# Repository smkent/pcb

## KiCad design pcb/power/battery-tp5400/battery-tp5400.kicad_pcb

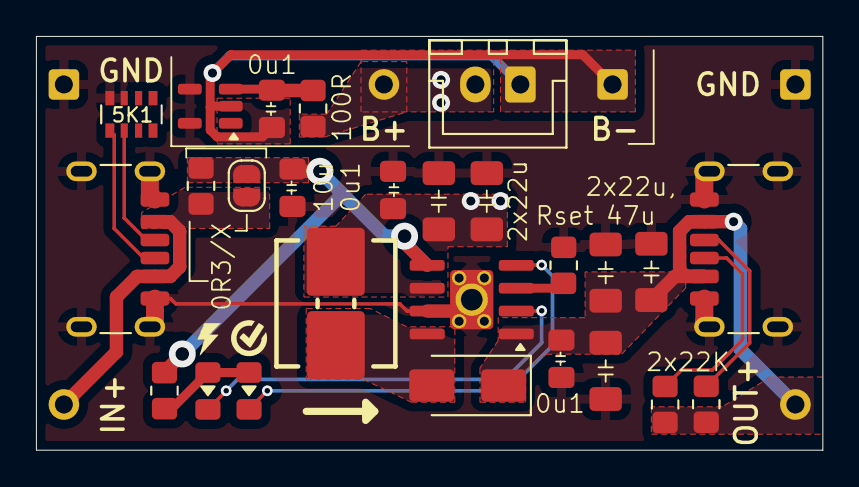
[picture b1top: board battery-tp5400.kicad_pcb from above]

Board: 2 copper layers, 43.7 x 23.0 mm, 32 parts (0 on the bottom side), 16 nets.

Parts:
BT1: Battery_Cell; JST_XH_B2B-XH-A_1x02_P2.50mm_Vertical_simple_pad2gnd
C0: 0.1uF; C_0805_2012Metric_Pad1.18x1.45mm_HandSolder
C1: 10u; C_0805_2012Metric_Pad1.18x1.45mm_HandSolder
C2, C5: 0u1; C_0805_2012Metric_Pad1.18x1.45mm_HandSolder
C3, C4, C6, C7: 22u; C_1206_3216Metric_Pad1.33x1.80mm_HandSolder
C8: 47u; C_1206_3216Metric_Pad1.33x1.80mm_HandSolder
D3: SS34; D_SMA
J0, J7: USB_C_Receptacle_PowerOnly_6P; USB_C_Receptacle_GCT_USB4125-xx-x_6P_TopMnt_Horizontal_hand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
J1, J3, J5: Conn_01x01; PinHeader_1x01_P2.54mm_simple
J2, J4, J6: Conn_01x01; PinHeader_1x01_P2.54mm_simple_square
JP1: SolderJumper_2_Open; SolderJumper-2_P1.3mm_Open_RoundedPad1.0x1.5mm
L2: 10u; Inductor_Multi_7.0x6.6_plus
LED1, LED2: LED; LED_0805_2012Metric_Pad1.15x1.40mm_HandSolder_simple
R0: 0R3; R_0805_2012Metric_Pad1.20x1.40mm_HandSolder
R1: 1K; R_0805_2012Metric_Pad1.20x1.40mm_HandSolder
R2: 100R; R_0805_2012Metric_Pad1.20x1.40mm_HandSolder
R3: 1K1; R_0805_2012Metric_Pad1.20x1.40mm_HandSolder
R4, R5: 22K; R_0805_2012Metric_Pad1.20x1.40mm_HandSolder
RN1: 5K1; R_Array_Convex_4x0603
U1: TP5400_C2891434; SOIC-8-1EP_3.9x4.9mm_P1.27mm_EP2.41x3.3mm_ThermalVias_Custo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
U2: XB5350D0; SOT-23-5_simple

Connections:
B+: BT1.1 (+), C2.2, C3.2, C4.2, J3.1, L2.2, R2.1, U1.6 (BAT)
B-: BT1.2 (-), C0.1, J4.1, U2.2 (GND)
BATVDD: C0.2, R2.2, U2.3 (VDD)
GND: C1.1, C2.1, C3.1, C4.1, C5.1, C6.1, C7.1, C8.1, J0.A12 (GND), J0.B12 (GND), J0.S1 (SHIELD), J2.1, J6.1, J7.A12 (GND), J7.B12 (GND), J7.S1 (SHIELD), R3.1, RN1.7 (R2.2), RN1.8 (R1.2), U1.7 (GND), U1.9 (EP), U2.4 (VM), U2.5 (VM)
LED1: LED1.1 (K), U1.2 (~CHRG)
LED2: LED2.1 (K), U1.4 (~STDBY)
LX: D3.2 (A), L2.1, U1.8 (LX)
unnamed: J0.A5 (CC1), RN1.2 (R2.1)
unnamed: J0.B5 (CC2), RN1.1 (R1.1)
unnamed: J7.A5 (CC1), R4.2
unnamed: J7.B5 (CC2), R5.2
unnamed: LED1.2 (A), LED2.2 (A), R1.2
unnamed: R3.2, U1.3 (PROG)
VCC: J0.A9 (VBUS), J0.B9 (VBUS), J1.1, JP1.2 (B), R0.2
VIN: C1.2, JP1.1 (A), R0.1, R1.1, U1.5 (VCC)
VOUT: C5.2, C6.2, C7.2, C8.2, D3.1 (K), J5.1, J7.A9 (VBUS), J7.B9 (VBUS), R4.1, R5.1, U1.1 (VOUT)

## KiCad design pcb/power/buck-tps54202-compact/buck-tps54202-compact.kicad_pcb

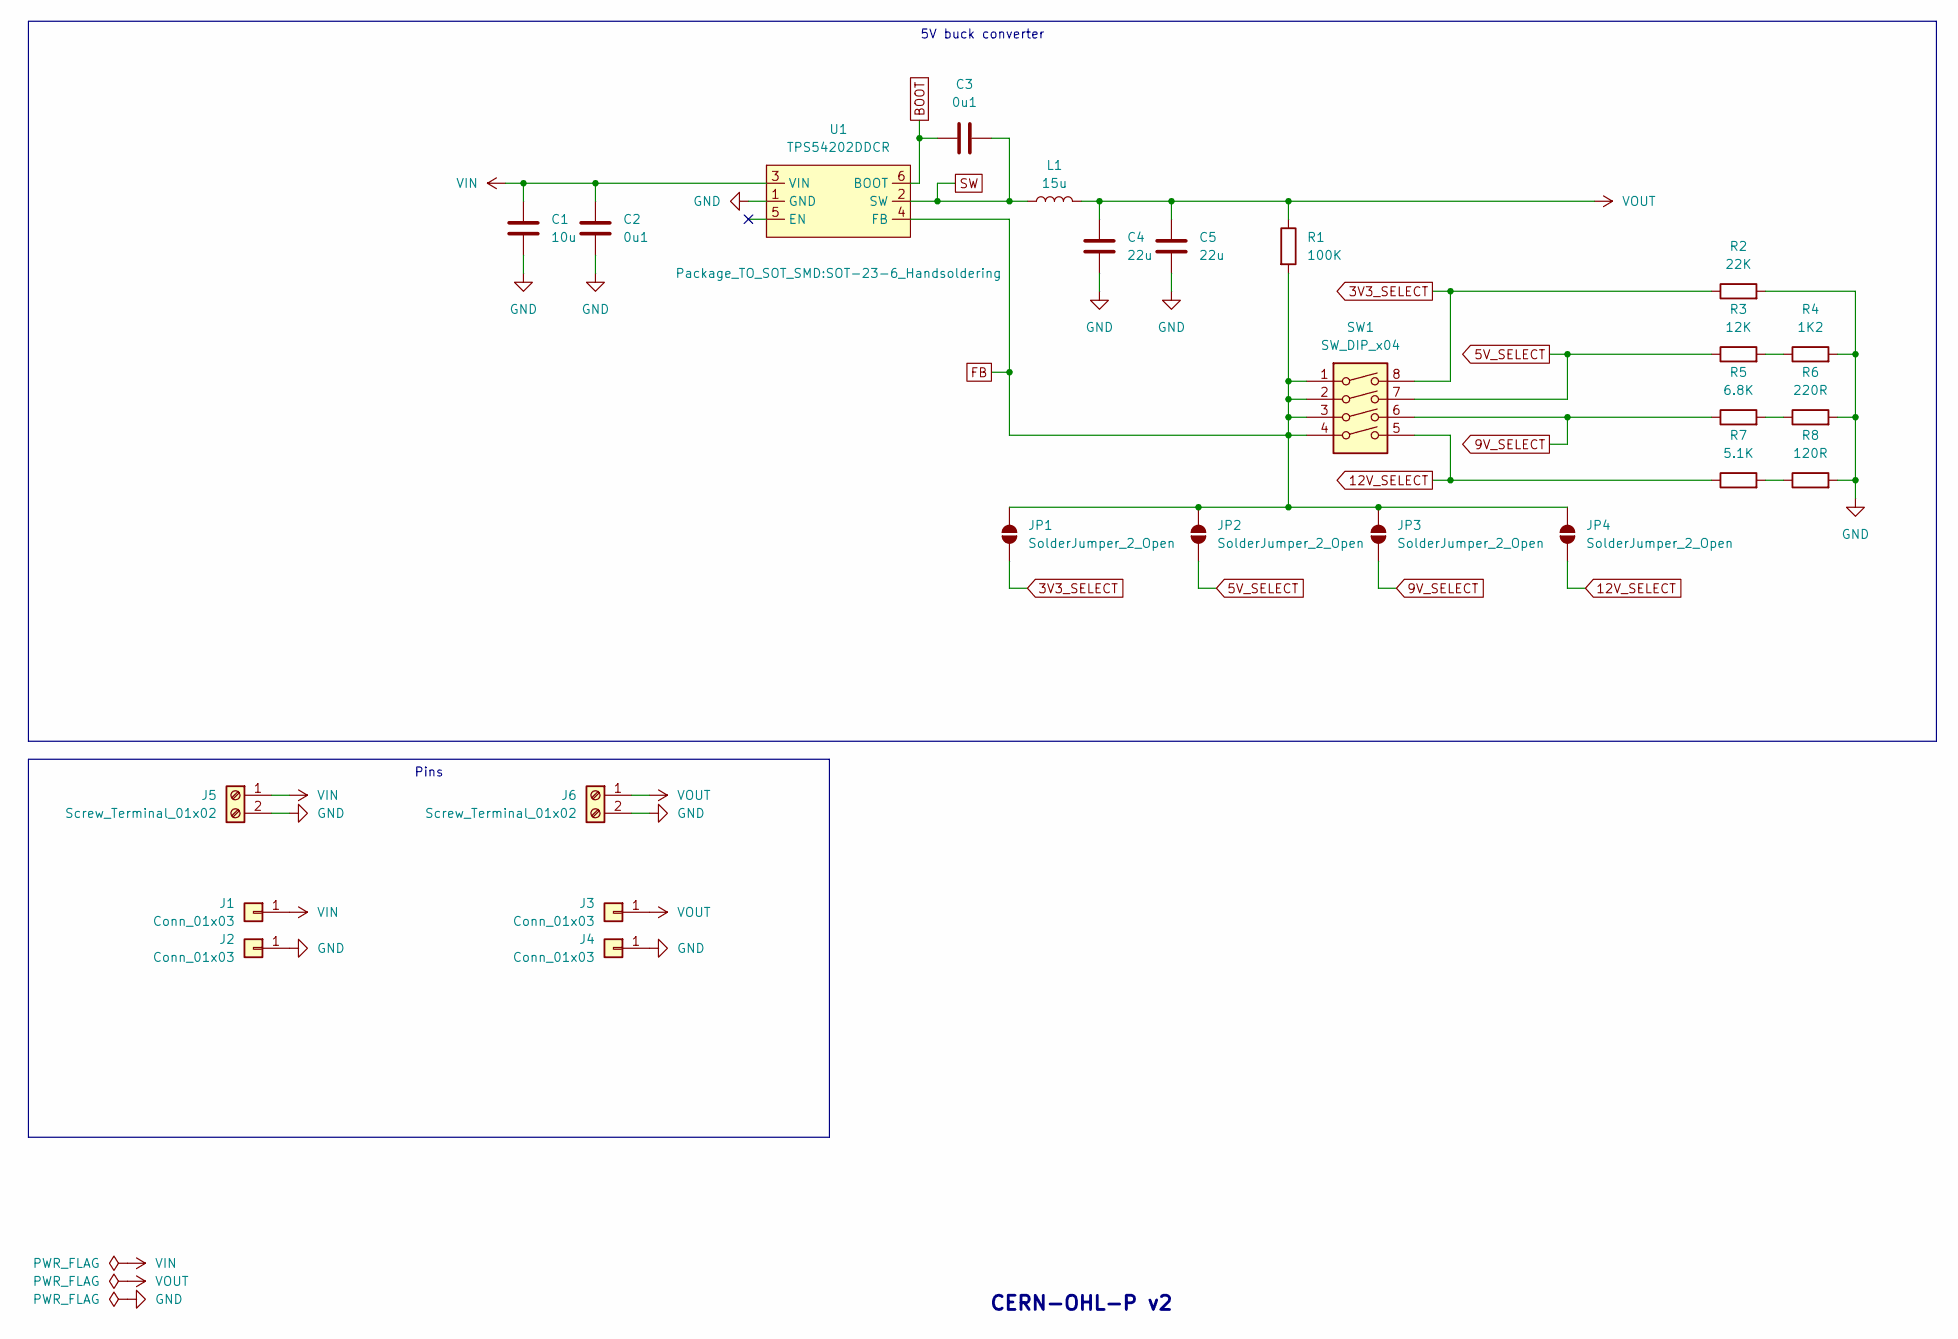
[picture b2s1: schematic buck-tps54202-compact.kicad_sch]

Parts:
C1: 10u; C_0805_2012Metric_Pad1.18x1.45mm_HandSolder; LCSC Part C440198
C2, C3: 0u1; C_0402_1005Metric; LCSC Part C307331
C4, C5: 22u; C_0805_2012Metric_Pad1.18x1.45mm_HandSolder; LCSC Part C45783
J1, J3: Conn_01x03; PinHeader_1x01_P2.54mm_simple
J2, J4: Conn_01x03; PinHeader_1x01_P2.54mm_simple_square
J5, J6: Screw_Terminal_01x02; TerminalBlock_or_JST_2.54_1x02
JP1, JP2, JP3, JP4: SolderJumper_2_Open; SolderJumper-2_P1.3mm_Open_RoundedPad1.0x1.5mm_simple
L1: 15u; Inductor_Multi_5.2x5.7_2x2.5
R1: 100K; R_0402_1005Metric; LCSC Part C25741
R2: 22K; R_0402_1005Metric; LCSC Part C25768
R3: 12K; R_0402_1005Metric; LCSC Part C25752
R4: 1K2; R_0402_1005Metric; LCSC Part C25862
R5: 6.8K; R_0402_1005Metric; LCSC Part C25917
R6: 220R; R_0402_1005Metric; LCSC Part C25091
R7: 5.1K; R_0402_1005Metric; LCSC Part C25905
R8: 120R; R_0402_1005Metric; LCSC Part C25079
SW1: SW_DIP_x04; SW_DIP_SPSTx04_Slide_P1.27mm_simple
U1: TPS54202DDCR; SOT-23-6_Handsoldering; LCSC Part C191884

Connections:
3V3_SELECT: JP1.1 (A), R2.1, SW1.8
5V_SELECT: JP2.1 (A), R3.1, SW1.7
9V_SELECT: JP3.1 (A), R5.1, SW1.6
12V_SELECT: JP4.1 (A), R7.1, SW1.5
BOOT: C3.1, U1.6 (BOOT)
FB: JP1.2 (B), JP2.2 (B), JP3.2 (B), JP4.2 (B), R1.2, SW1.1, SW1.2, SW1.3, SW1.4, U1.4 (FB)
GND: C1.2, C2.2, C4.2, C5.2, J2.1, J4.1, J5.2, J6.2, R2.2, R4.2, R6.2, R8.2, U1.1 (GND)
unnamed: R3.2, R4.1
unnamed: R5.2, R6.1
unnamed: R7.2, R8.1
SW: C3.2, L1.1, U1.2 (SW)
VIN: C1.1, C2.1, J1.1, J5.1, U1.3 (VIN)
VOUT: C4.1, C5.1, J3.1, J6.1, L1.2, R1.1

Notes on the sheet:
5V buck converter
Pins
CERN-OHL-P v2

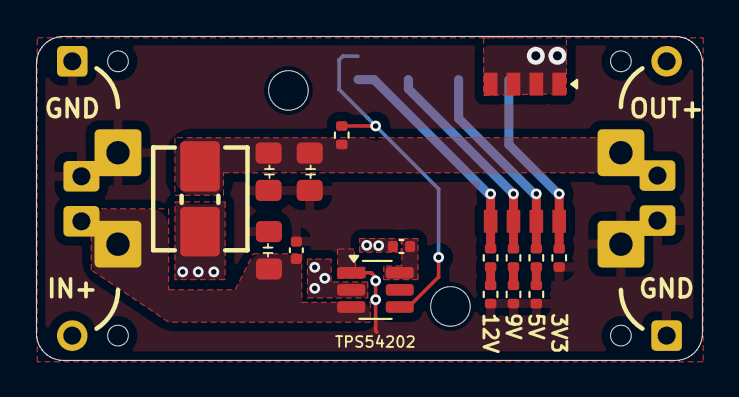
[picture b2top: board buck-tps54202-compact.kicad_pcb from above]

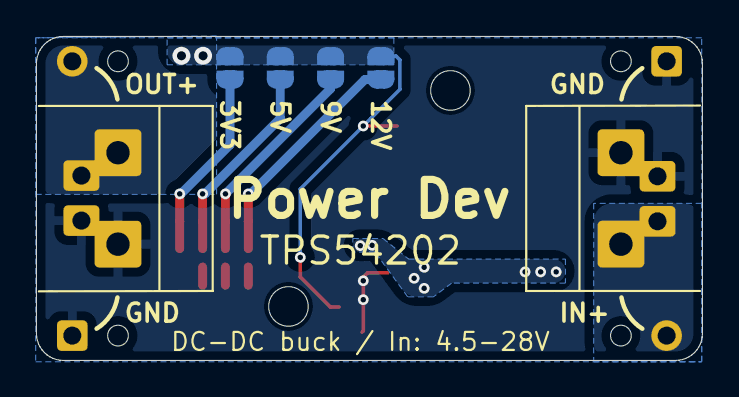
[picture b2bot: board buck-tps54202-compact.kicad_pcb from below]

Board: 2 copper layers, 37.0 x 18.0 mm, 26 parts (10 on the bottom side), 13 nets.

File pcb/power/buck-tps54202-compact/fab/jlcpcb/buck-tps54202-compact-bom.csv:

Comment,Designator,Footprint,LCSC
Conn_01x03,"J1,J3",custom:PinHeader_1x01_P2.54mm_simple,
100K,R1,Resistor_SMD:R_0402_1005Metric,C25741
1K2,R4,Resistor_SMD:R_0402_1005Metric,C25862
Screw_Terminal_01x02,"J5,J6",custom:TerminalBlock_or_JST_2.54_1x02,
22u,"C4,C5",custom:C_0805_2012Metric_Pad1.18x1.45mm_HandSolder,C45783
SW_DIP_x04,SW1,custom:SW_DIP_SPSTx04_Slide_P1.27mm_simple,
10u,C1,custom:C_0805_2012Metric_Pad1.18x1.45mm_HandSolder,C440198
Conn_01x03,"J2,J4",custom:PinHeader_1x01_P2.54mm_simple_square,
6.8K,R5,Resistor_SMD:R_0402_1005Metric,C25917
120R,R8,Resistor_SMD:R_0402_1005Metric,C25079
TPS54202DDCR,U1,Package_TO_SOT_SMD:SOT-23-6_Handsoldering,C191884
5.1K,R7,Resistor_SMD:R_0402_1005Metric,C25905
15u,L1,custom:Inductor_Multi_5.2x5.7_2x2.5,
0u1,"C2,C3",Capacitor_SMD:C_0402_1005Metric,C307331
22K,R2,Resistor_SMD:R_0402_1005Metric,C25768
12K,R3,Resistor_SMD:R_0402_1005Metric,C25752
220R,R6,Resistor_SMD:R_0402_1005Metric,C25091

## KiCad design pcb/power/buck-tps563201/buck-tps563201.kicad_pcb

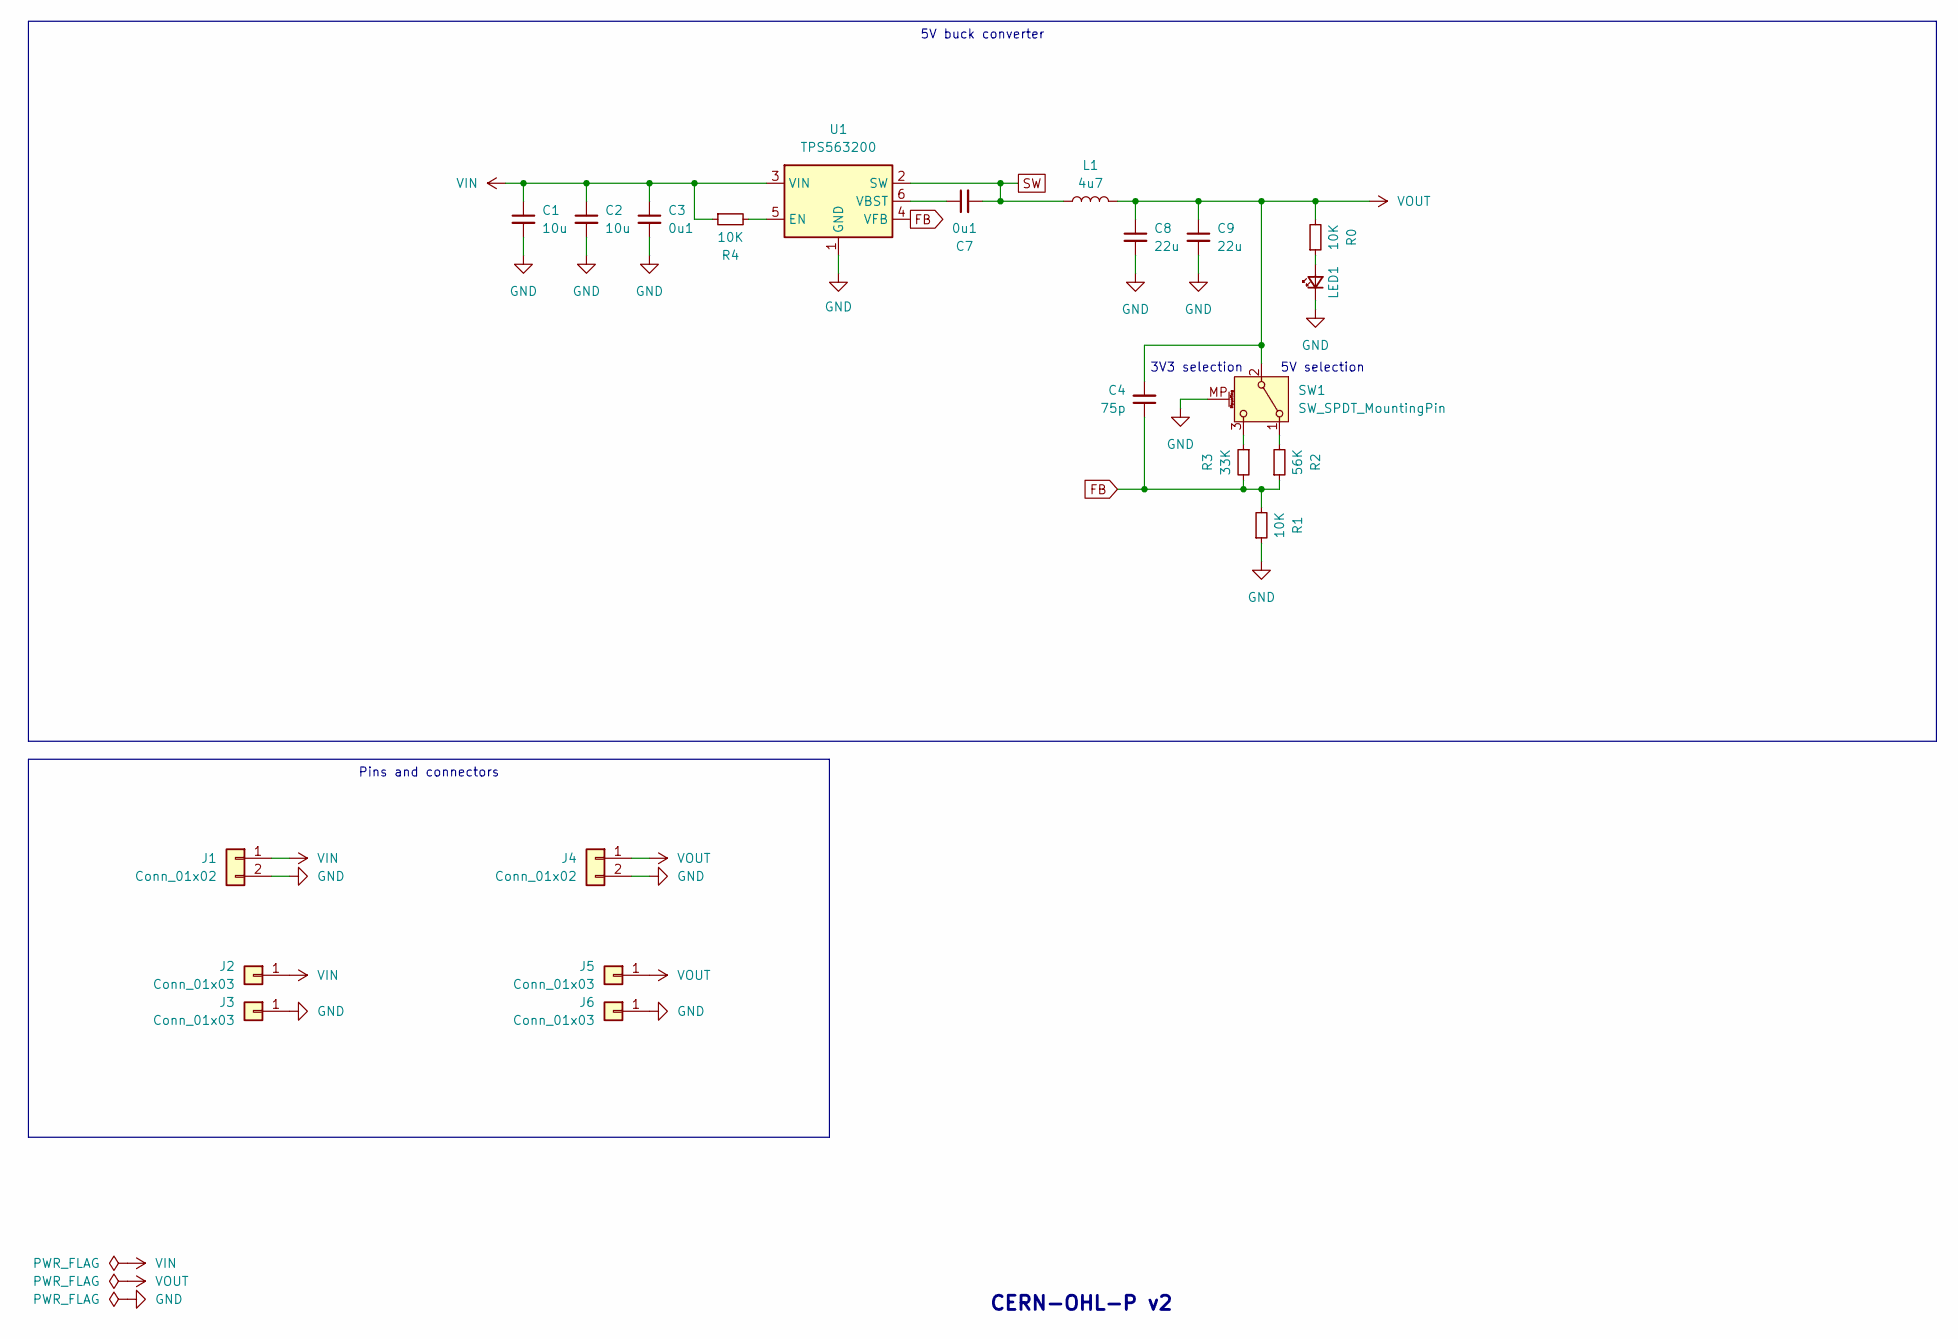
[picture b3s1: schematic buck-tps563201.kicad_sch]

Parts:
C1, C2: 10u; C_0603_1608Metric_Pad1.08x0.95mm_HandSolder
C3, C7: 0u1; C_0603_1608Metric_Pad1.08x0.95mm_HandSolder
C4: 75p; C_0603_1608Metric_Pad1.08x0.95mm_HandSolder
C8, C9: 22u; C_0805_2012Metric_Pad1.18x1.45mm_HandSolder
J1, J4: Conn_01x02; Conn_Combo_JST-1x02-XH_PH-THT-pad2gnd
J2, J5: Conn_01x03; PinHeader_1x01_P2.54mm_simple
J3, J6: Conn_01x03; PinHeader_1x01_P2.54mm_simple_square
L1: 4u7; Inductor_Multi_5.2x5.7_2x2.5
LED1: LED_Small; LED_0603_1608Metric_Pad1.05x0.95mm_HandSolder_simple
R0, R1, R4: 10K; R_0603_1608Metric_Pad0.98x0.95mm_HandSolder
R2: 56K; R_0603_1608Metric_Pad0.98x0.95mm_HandSolder
R3: 33K; R_0603_1608Metric_Pad0.98x0.95mm_HandSolder
SW1: SW_SPDT_MountingPin; SW_SPDT_PCM12
U1: TPS563200; SOT-23-6

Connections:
FB: C4.1, R1.2, R2.1, R3.2, U1.4 (VFB)
GND: C1.2, C2.2, C3.2, C8.2, C9.2, J1.2, J3.1, J4.2, J6.1, LED1.1 (K), R1.1, SW1.MP (MountPin), U1.1 (GND)
unnamed: LED1.2 (A), R0.1
unnamed: R2.2, SW1.1 (A)
unnamed: R3.1, SW1.3 (C)
unnamed: R4.2, U1.5 (EN)
unnamed: C7.1, U1.6 (VBST)
SW: C7.2, L1.1, U1.2 (SW)
VIN: C1.1, C2.1, C3.1, J1.1, J2.1, R4.1, U1.3 (VIN)
VOUT: C4.2, C8.1, C9.1, J4.1, J5.1, L1.2, R0.2, SW1.2 (B)

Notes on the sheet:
Pins and connectors
5V buck converter
CERN-OHL-P v2
3V3 selection
5V selection

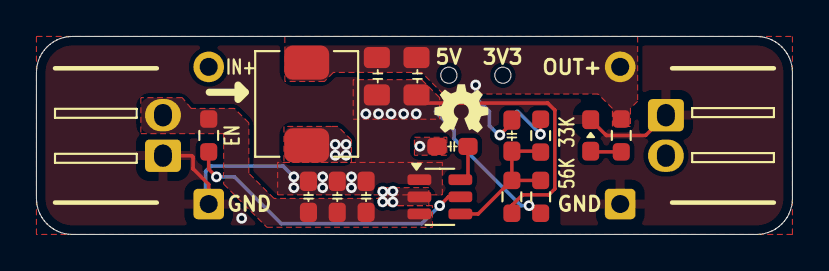
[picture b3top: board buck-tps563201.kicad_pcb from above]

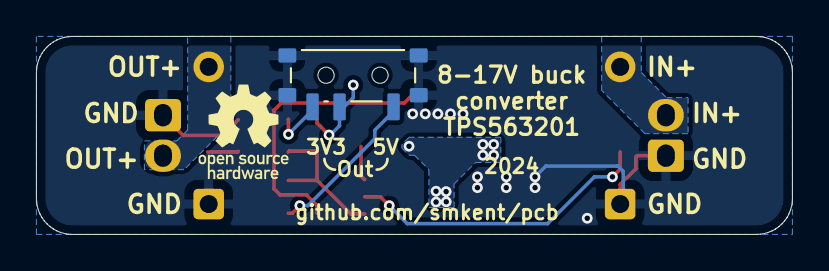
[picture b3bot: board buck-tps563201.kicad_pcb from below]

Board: 2 copper layers, 42.0 x 11.0 mm, 22 parts (5 on the bottom side), 10 nets.

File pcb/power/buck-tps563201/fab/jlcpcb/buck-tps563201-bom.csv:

Comment,Designator,Footprint,LCSC
0u1,"C3,C7",custom:C_0603_1608Metric_Pad1.08x0.95mm_HandSolder,
TPS563200,U1,custom:SOT-23-6_Handsoldering_simple,
LED_Small,LED1,custom:LED_0603_1608Metric_Pad1.05x0.95mm_HandSolder_simple,
56K,R2,Resistor_SMD:R_0603_1608Metric_Pad0.98x0.95mm_HandSolder,
Conn_01x03,"J2,J5",custom:PinHeader_1x01_P2.54mm_simple,
Conn_01x03,"J3,J6",custom:PinHeader_1x01_P2.54mm_simple_square,
22u,"C8,C9",custom:C_0805_2012Metric_Pad1.18x1.45mm_HandSolder,
75p,C4,custom:C_0603_1608Metric_Pad1.08x0.95mm_HandSolder,
33K,R3,Resistor_SMD:R_0603_1608Metric_Pad0.98x0.95mm_HandSolder,
4u7,L1,custom:Inductor_Multi_5.2x5.7_2x2.5,
SW_SPDT,SW1,lcsc:SW-SMD_3P-P1.50_L2.7-W6.6,
10K,"R0,R1,R4",Resistor_SMD:R_0603_1608Metric_Pad0.98x0.95mm_HandSolder,
Conn_01x02,"J1,J4",custom:Conn_Combo_JST-1x02-XH_PH-THT-pad2gnd,
10u,"C1,C2",custom:C_0603_1608Metric_Pad1.08x0.95mm_HandSolder,

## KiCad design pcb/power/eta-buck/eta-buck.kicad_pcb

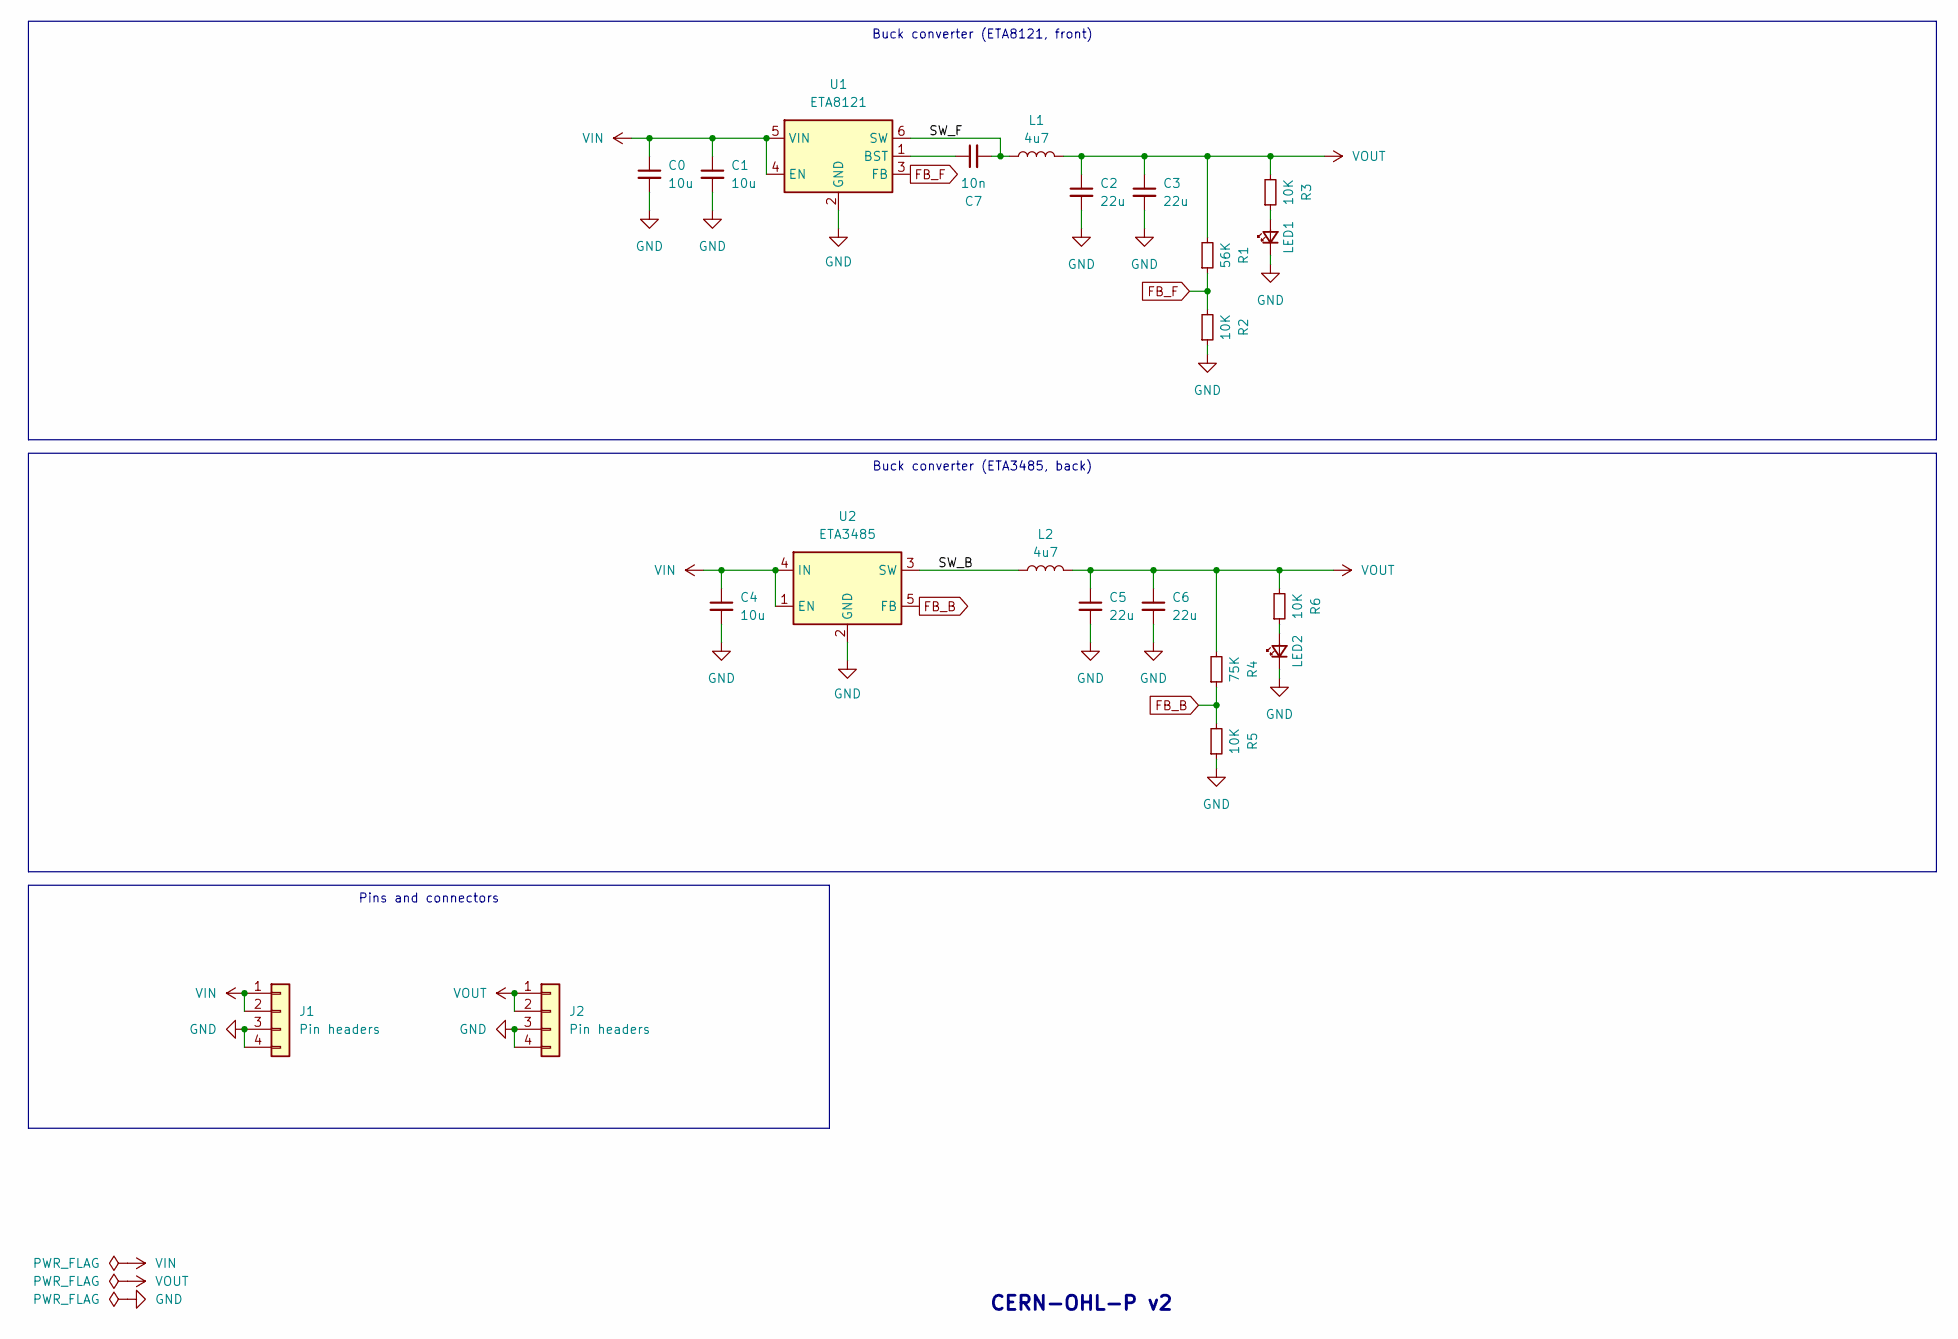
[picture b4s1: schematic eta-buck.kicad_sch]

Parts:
C0, C1, C4: 10u; C_0603_1608Metric_Pad1.08x0.95mm_HandSolder
C2, C3, C5, C6: 22u; C_0603_1608Metric_Pad1.08x0.95mm_HandSolder
C7: 10n; C_0603_1608Metric_Pad1.08x0.95mm_HandSolder
J1, J2: Pin headers; PinHeader_1x04_P2.54mm_Vertical_simple_pad3,4gnd
L1, L2: 4u7; L_1008_2520Metric
LED1, LED2: LED_Small; LED_0603_1608Metric_Pad1.05x0.95mm_HandSolder_simple
R1: 56K; R_0603_1608Metric_Pad0.98x0.95mm_HandSolder
R2, R3, R5, R6: 10K; R_0603_1608Metric_Pad0.98x0.95mm_HandSolder
R4: 75K; R_0603_1608Metric_Pad0.98x0.95mm_HandSolder
U1: ETA8121; SOT-23-6; LCSC Part C7465509
U2: ETA3485; SOT-23-5; LCSC Part C7465518

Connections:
/SW_B: L2.1, U2.3 (SW)
/SW_F: C7.2, L1.1, U1.6 (SW)
FB_B: R4.1, R5.2, U2.5 (FB)
FB_F: R1.1, R2.2, U1.3 (FB)
GND: C0.2, C1.2, C2.2, C3.2, C4.2, C5.2, C6.2, J1.3, J1.4, J2.3, J2.4, LED1.1 (K), LED2.1 (K), R2.1, R5.1, U1.2 (GND), U2.2 (GND)
unnamed: LED1.2 (A), R3.1
unnamed: LED2.2 (A), R6.1
unnamed: C7.1, U1.1 (BST)
VIN: C0.1, C1.1, C4.1, J1.1, J1.2, U1.4 (EN), U1.5 (VIN), U2.1 (EN), U2.4 (IN)
VOUT: C2.1, C3.1, C5.1, C6.1, J2.1, J2.2, L1.2, L2.2, R1.2, R3.2, R4.2, R6.2

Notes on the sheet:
Pins and connectors
Buck converter (ETA8121, front)
Buck converter (ETA3485, back)
CERN-OHL-P v2

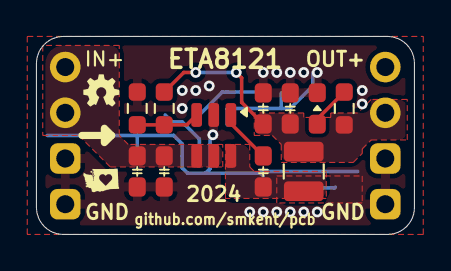
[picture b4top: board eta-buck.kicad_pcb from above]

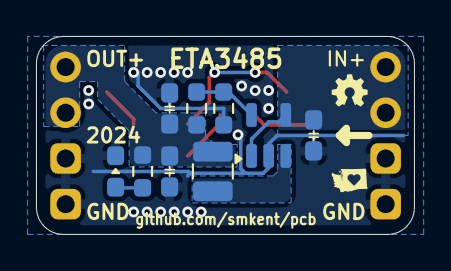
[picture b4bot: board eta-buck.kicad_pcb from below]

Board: 2 copper layers, 21.0 x 11.0 mm, 22 parts (11 on the bottom side), 10 nets.

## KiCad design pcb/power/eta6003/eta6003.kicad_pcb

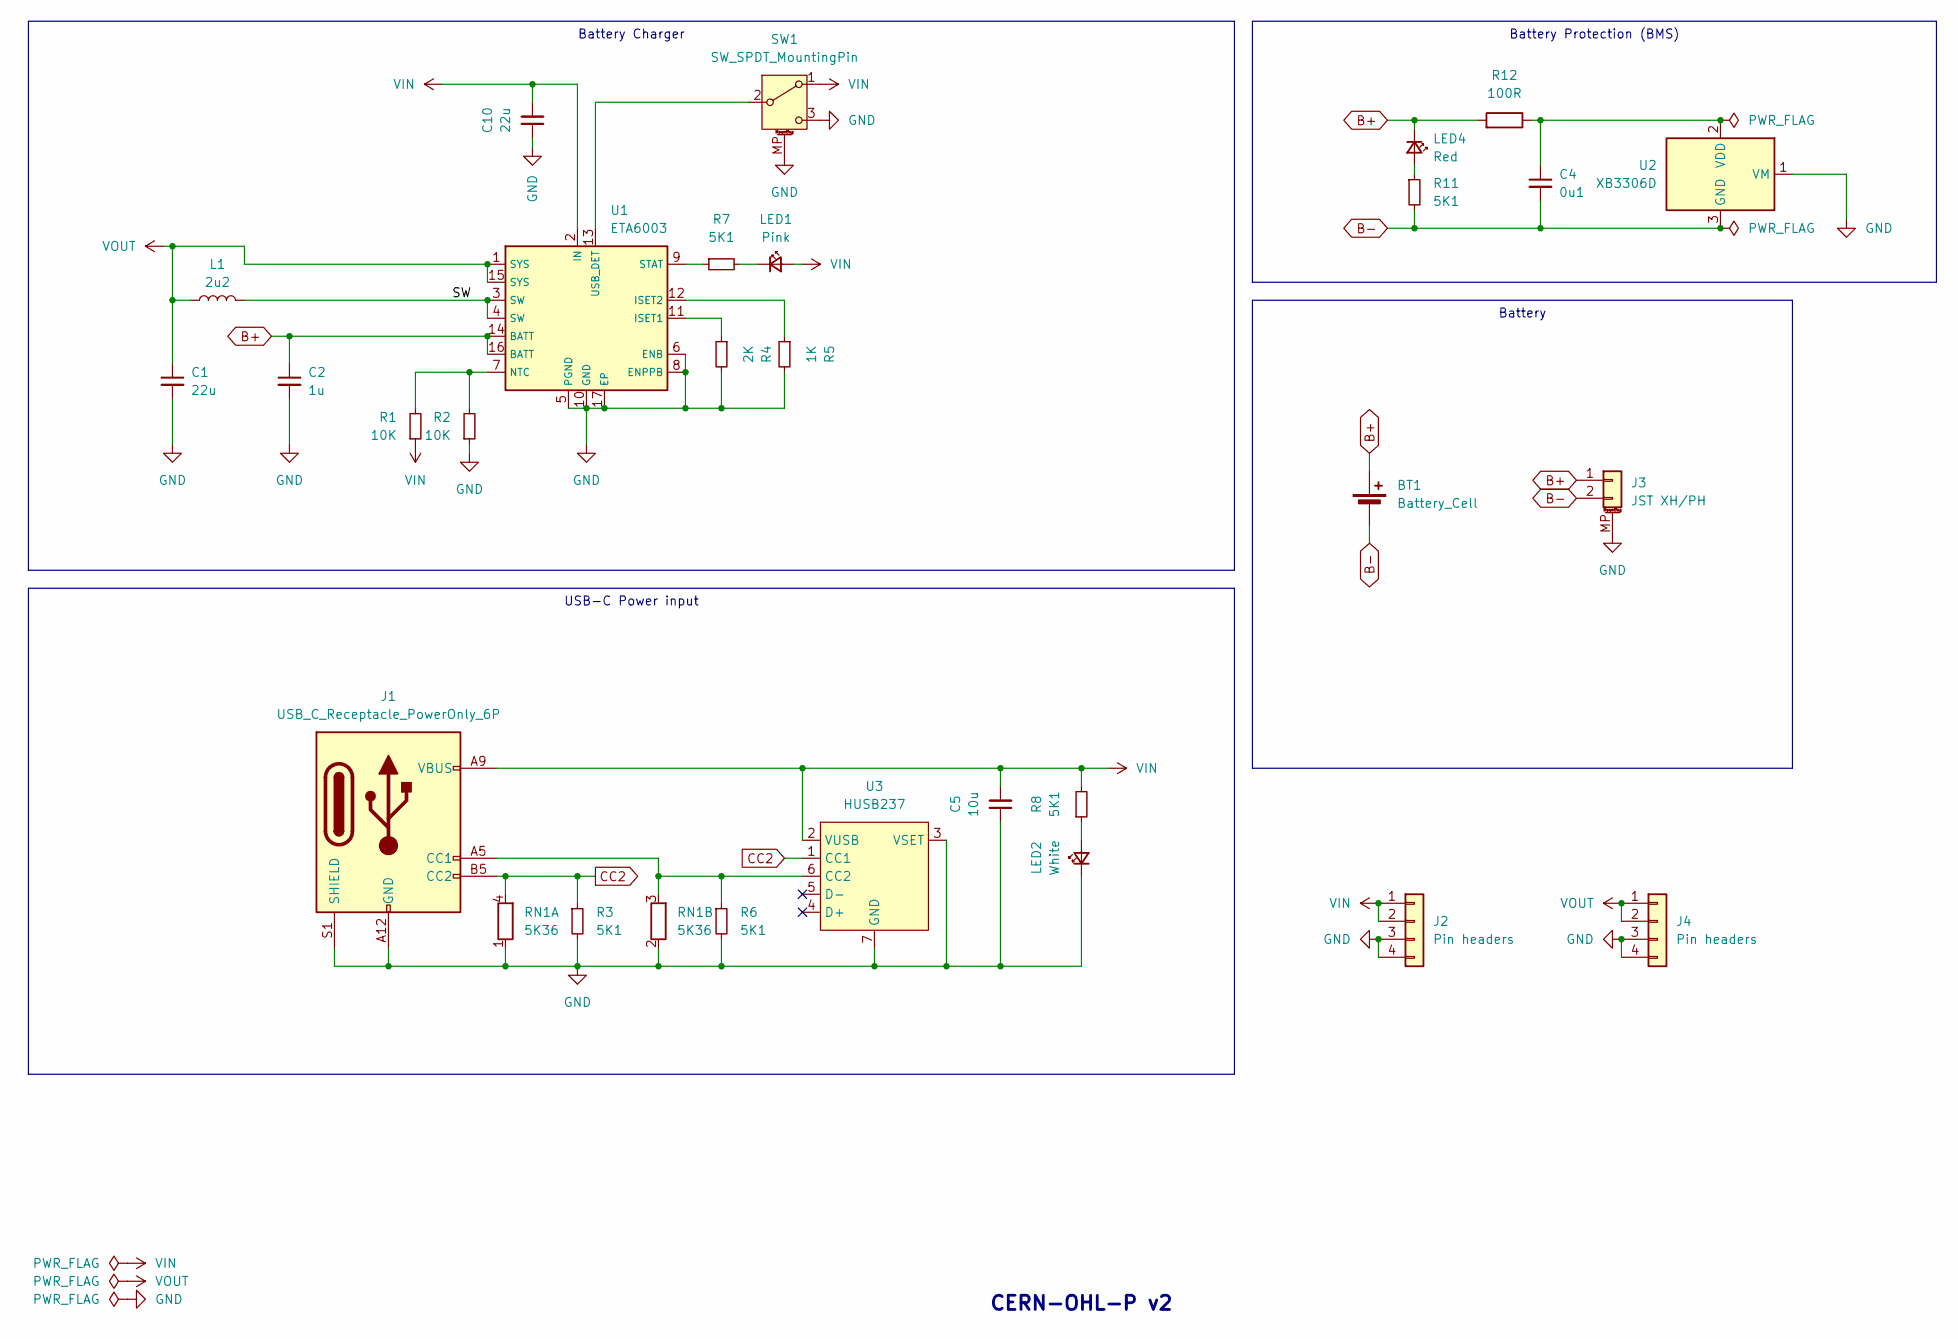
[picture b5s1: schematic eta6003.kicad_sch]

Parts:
BT1: Battery_Cell; BatteryHolder_1x18650_THT
C1: 22u; C_0603_1608Metric_Pad1.08x0.95mm_HandSolder; LCSC Part C45783
C2: 1u; C_0603_1608Metric_Pad1.08x0.95mm_HandSolder; LCSC Part C52923
C4: 0u1; C_0603_1608Metric_Pad1.08x0.95mm_HandSolder; LCSC Part C1525
C5: 10u; C_0603_1608Metric_Pad1.08x0.95mm_HandSolder; LCSC Part C15850
C10: 22u; C_0805_2012Metric_Pad1.18x1.45mm_HandSolder_wide-center; LCSC Part C15850
J1: USB_C_Receptacle_PowerOnly_6P; USB_C_Receptacle_GCT_USB4125-xx-x_6P_TopMnt_Horizontal_Hand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; LCSC Part C2927029
J2, J4: Pin headers; PinHeader_1x04_P2.54mm_Vertical_simple_pad3,4gnd
J3: JST XH/PH; Conn_Combo_JST-1x02-XH_PH-SMD-alt-pad2gnd
L1: 2u2; L_1008_2520Metric; LCSC Part C5832372
LED1: Pink; LED_0603_1608Metric_Pad1.05x0.95mm_HandSolder_simple
LED2: White; LED_0603_1608Metric_Pad1.05x0.95mm_HandSolder_simple
LED4: Red; LED_0603_1608Metric_Pad1.05x0.95mm_HandSolder_simple; LCSC Part C2286
R1, R2: 10K; R_0603_1608Metric_Pad0.98x0.95mm_HandSolder; LCSC Part C25744
R3, R6, R11: 5K1; R_0603_1608Metric_Pad0.98x0.95mm_HandSolder; LCSC Part C25905
R4: 2K; R_0603_1608Metric_Pad0.98x0.95mm_HandSolder; LCSC Part C22975
R5: 1K; R_0603_1608Metric_Pad0.98x0.95mm_HandSolder; LCSC Part C21190
R7, R8: 5K1; R_0603_1608Metric_Pad0.98x0.95mm_HandSolder; LCSC Part C21190
R12: 100R; R_0603_1608Metric_Pad0.98x0.95mm_HandSolder; LCSC Part C25076
RN1: 5K36; R_Array_Convex_2x0402
SW1: SW_SPDT_MountingPin; SW_SPDT_PCM12
U1: ETA6003; QFN-16-1EP_3x3mm_P0.5mm_EP1.7x1.7mm_ThermalVias_ETA6003; LCSC Part C5455585
U2: XB3306D; SOT-23; LCSC Part C2759992
U3: HUSB237; DFN-6-1EP_2x2mm_P0.65mm_EP1x1.6mm; LCSC Part C7471904

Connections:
/SW: L1.2, U1.3 (SW), U1.4 (SW)
B+: BT1.1 (+), C2.1, J3.1, LED4.1 (K), R12.2, U1.14 (BATT), U1.16 (BATT)
B-: BT1.2 (-), C4.2, J3.2, R11.2, U2.3 (GND)
CC2: J1.B5 (CC2), R3.1, RN1.4 (R1.2), U3.1 (CC1)
GND: C1.2, C2.2, C5.1, C10.1, J1.A12 (GND), J1.B12 (GND), J1.S1 (SHIELD), J2.3, J2.4, J3.MP (MountPin), J4.3, J4.4, LED2.1 (K), R2.1, R3.2, R4.2, R5.2, R6.2, RN1.1 (R1.1), RN1.2 (R2.1), SW1.3 (C), SW1.MP (MountPin), U1.5 (PGND), U1.6 (ENB), U1.8 (ENPPB), U1.10 (GND), U1.17 (EP), U2.1 (VM), U3.3 (VSET), U3.7 (GND)
unnamed: J1.A5 (CC1), R6.1, RN1.3 (R2.2), U3.6 (CC2)
unnamed: LED1.1 (K), R7.2
unnamed: LED2.2 (A), R8.1
unnamed: LED4.2 (A), R11.1
unnamed: SW1.2 (B), U1.13 (USB_DET)
unnamed: R4.1, U1.11 (ISET1)
unnamed: R5.1, U1.12 (ISET2)
unnamed: R1.2, R2.2, U1.7 (NTC)
unnamed: R7.1, U1.9 (STAT)
unnamed: C4.1, R12.1, U2.2 (VDD)
VIN: C5.2, C10.2, J1.A9 (VBUS), J1.B9 (VBUS), J2.1, J2.2, LED1.2 (A), R1.1, R8.2, SW1.1 (A), U1.2 (IN), U3.2 (VUSB)
VOUT: C1.1, J4.1, J4.2, L1.1, U1.1 (SYS), U1.15 (SYS)

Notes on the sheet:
USB-C Power input
Battery Protection (BMS)
Battery Charger
Battery
CERN-OHL-P v2

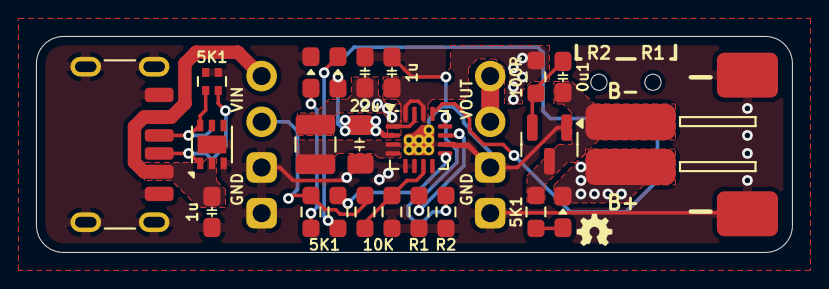
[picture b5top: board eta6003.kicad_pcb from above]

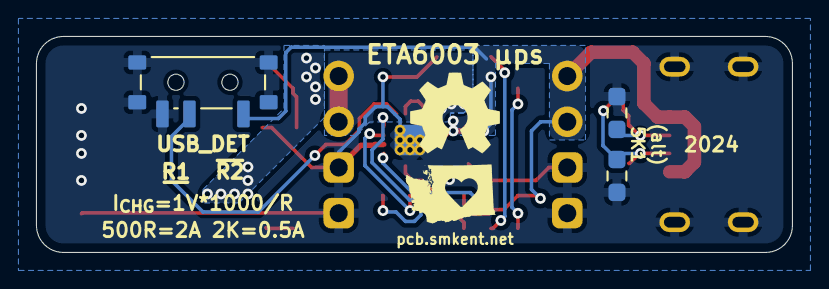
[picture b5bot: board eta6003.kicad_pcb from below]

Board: 2 copper layers, 42.0 x 12.0 mm, 28 parts (5 on the bottom side), 17 nets.

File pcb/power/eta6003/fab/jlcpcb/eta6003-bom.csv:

Comment,Designator,Footprint,LCSC
2u2,L1,lcsc:IND-SMD_L2.5-W2.0_MHCHL2520,C5832372
10K,"R1,R2",custom:R_0603_1608Metric_Pad0.98x0.95mm_HandSolder_simple,C25744
White,LED2,custom:LED_0603_1608Metric_Pad1.05x0.95mm_HandSolder_simple,
Pink,LED1,custom:LED_0603_1608Metric_Pad1.05x0.95mm_HandSolder_simple,
Red,LED4,custom:LED_0603_1608Metric_Pad1.05x0.95mm_HandSolder_simple,C2286
5K1,"R7,R8",custom:R_0603_1608Metric_Pad0.98x0.95mm_HandSolder_simple, C21190
Pin headers,"J2,J4","custom:PinHeader_1x04_P2.54mm_Vertical_simple_pad3,4gnd",
5K1,"R3,R6,R11",custom:R_0603_1608Metric_Pad0.98x0.95mm_HandSolder_simple,C25905
100R,R12,custom:R_0603_1608Metric_Pad0.98x0.95mm_HandSolder_simple,C25076
USB_C_Receptacle_PowerOnly_6P,J1,custom:USB_C_Receptacle_GCT_USB4125-xx-x_6P_TopMnt_Horizontal_handsolder,C2927029
0u1,C4,custom:C_0603_1608Metric_Pad1.08x0.95mm_HandSolder,C1525
SW_SPDT_MountingPin,SW1,lcsc:SW-SMD_3P-P1.50_L2.7-W6.6,
1u,C2,custom:C_0603_1608Metric_Pad1.08x0.95mm_HandSolder,C52923
22u,C10,custom:C_0805_2012Metric_Pad1.18x1.45mm_wide-center_HandSolder,C15850
5K36,RN1,Resistor_SMD:R_Array_Convex_2x0402,
1K,R5,Resistor_SMD:R_0603_1608Metric_Pad0.98x0.95mm_HandSolder, C21190
10u,C5,custom:C_0603_1608Metric_Pad1.08x0.95mm_HandSolder,C15850
22u,C1,custom:C_0603_1608Metric_Pad1.08x0.95mm_HandSolder,C45783
XB3306D,U2,custom:SOT-23_simple,C2759992
JST XH/PH,J3,custom:Conn_Combo_JST-1x02-XH_PH-SMD-alt-pad2gnd,
ETA6003,U1,custom:ETA6003_QFN-16-1EP_3x3mm_P0.5mm_EP1.7x1.7mm_ThermalVias,C5455585
2K,R4,Resistor_SMD:R_0603_1608Metric_Pad0.98x0.95mm_HandSolder, C22975
HUSB237,U3,Package_DFN_QFN:DFN-6-1EP_2x2mm_P0.65mm_EP1x1.6mm,C7471904
